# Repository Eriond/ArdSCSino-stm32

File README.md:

# Please read the following carefully:
This is a fork from the original ztto/ArdSCSino-stm32 project.\
This forks' only content are updated and modified versions of the PCB related files for the V2 version.\
The complete ztto/ArdSCSino-stm32 project is released under the MIT license, please respect that! It is only the files contained within this specific fork (Eriond/ArdSCSino-stm32) that are licensed under CC0 / Public Domain.

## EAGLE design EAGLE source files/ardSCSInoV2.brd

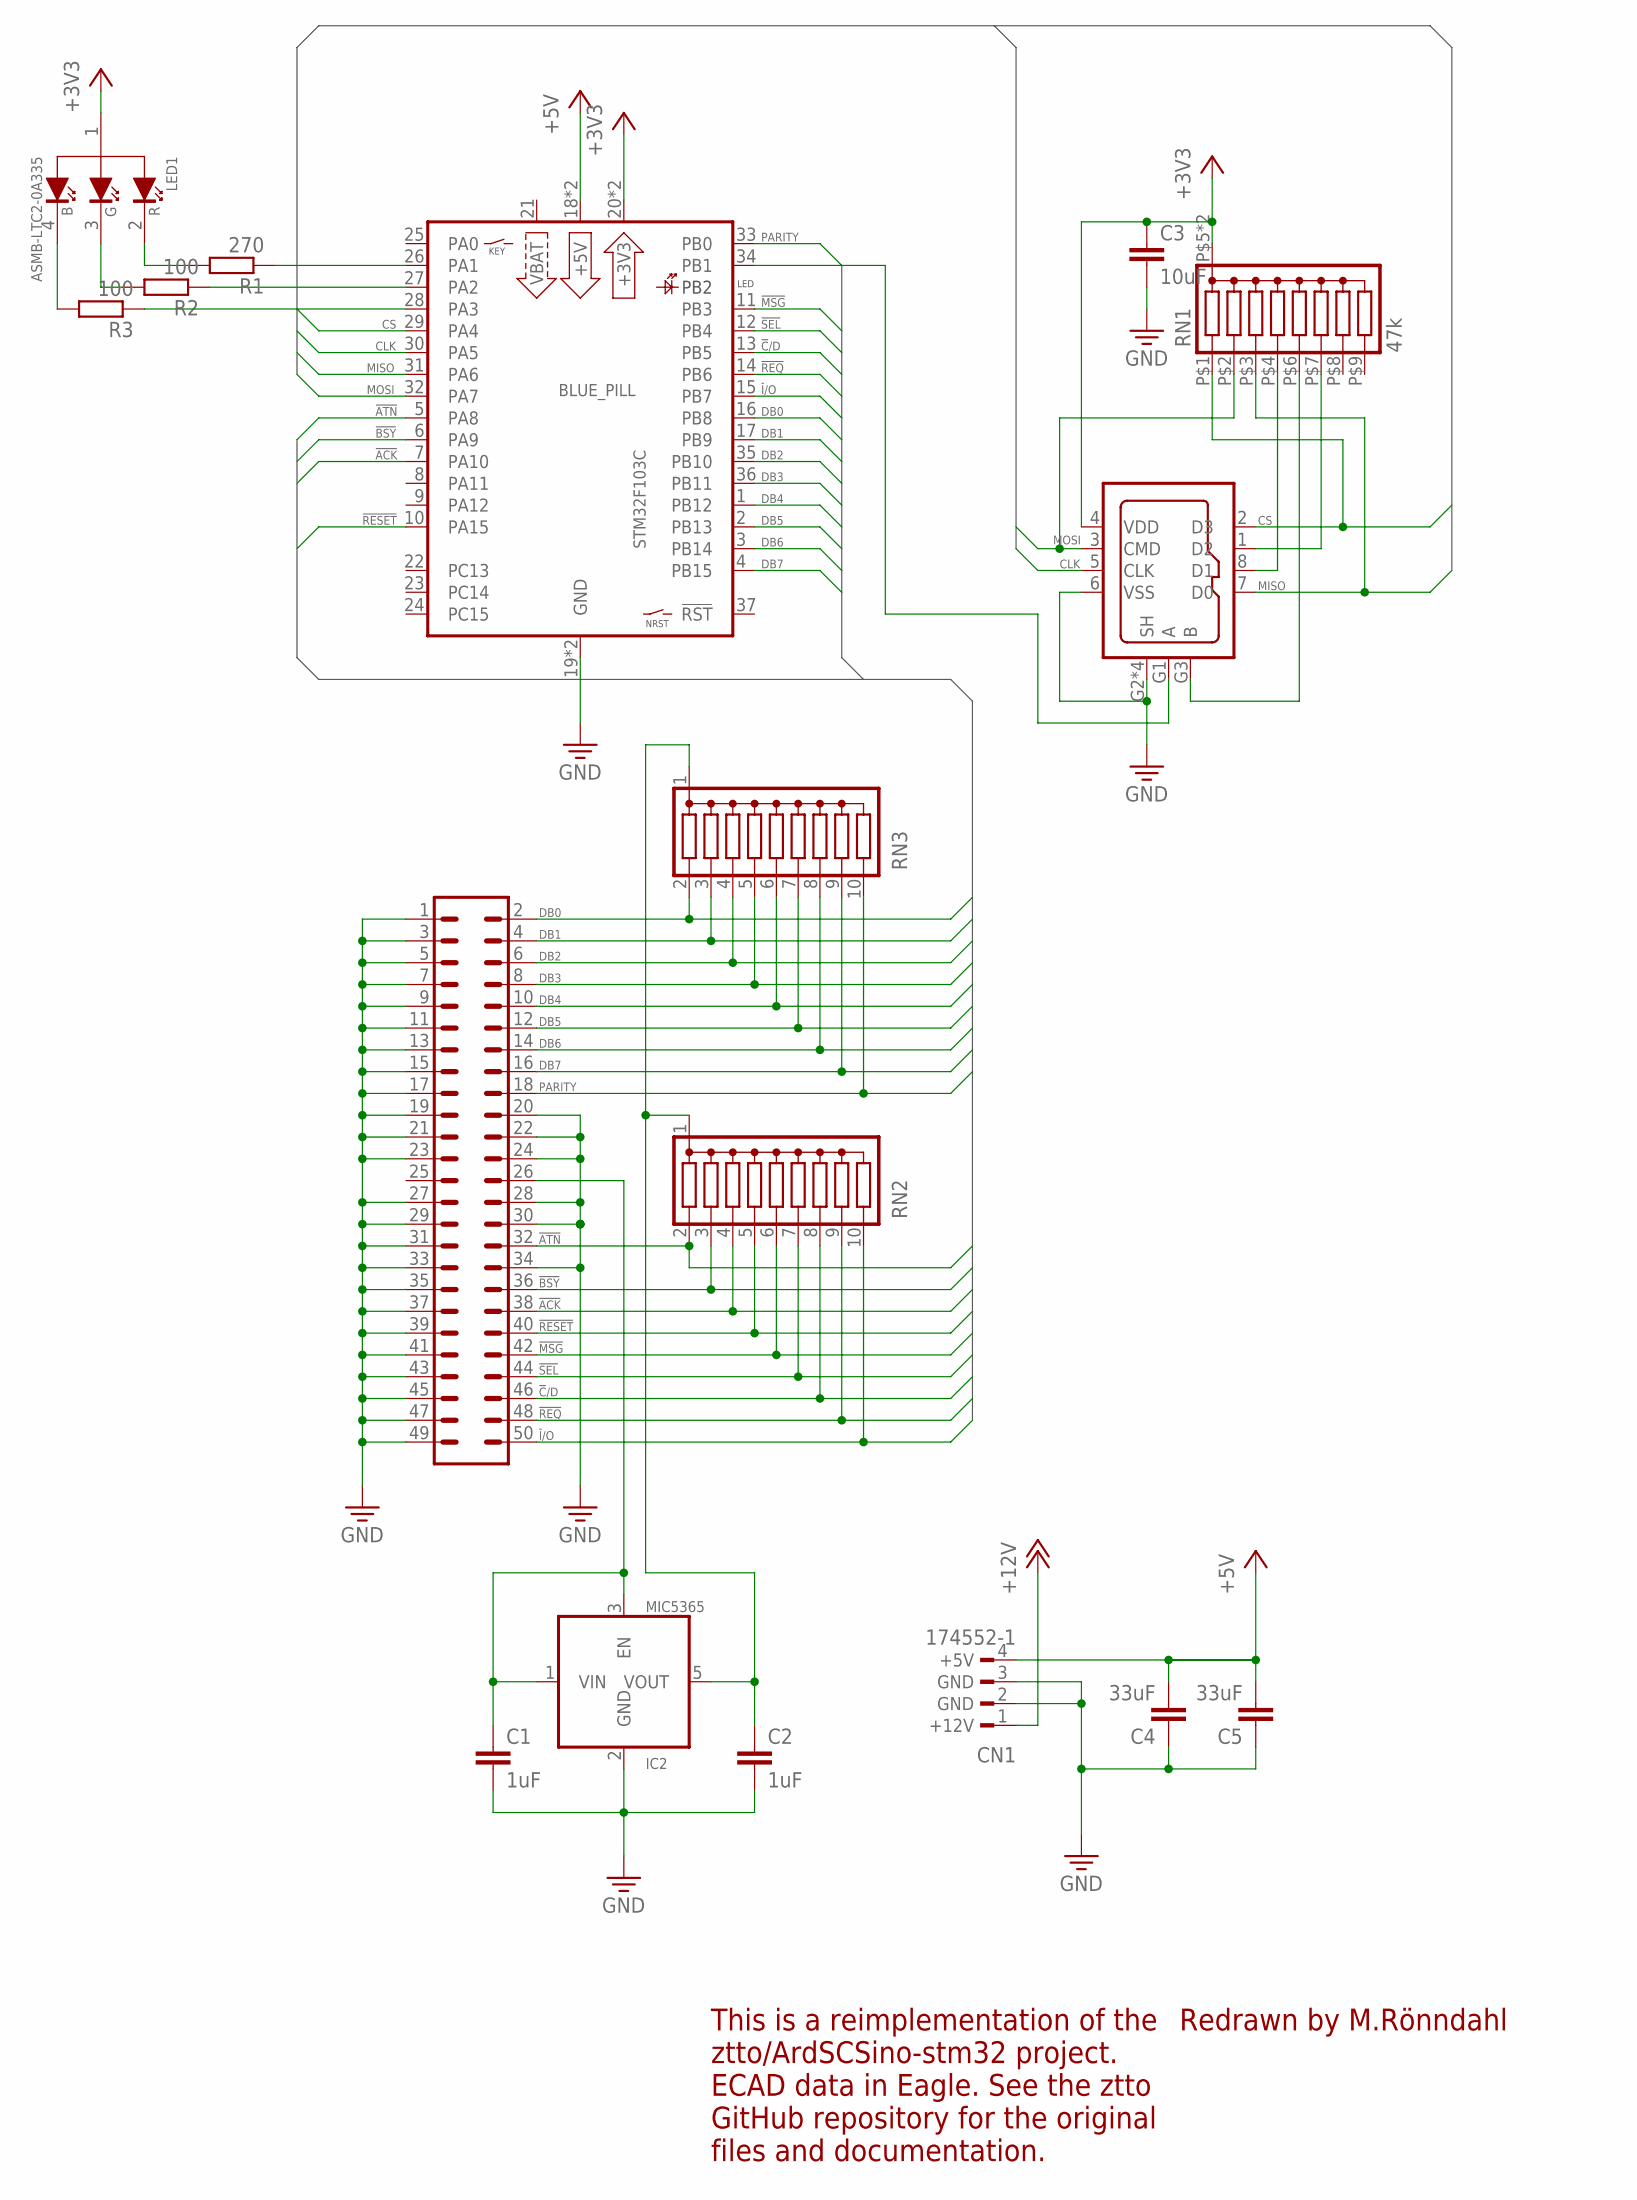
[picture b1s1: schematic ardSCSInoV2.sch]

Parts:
BLUE_PILL: STM32F103C; B-PILL
C1, C2: 1uF; C0805
C3: 10uF; C0805
C4, C5: 33uF; C0805
CN1: 174552-1
CN2: 30350-5002HB; 30350-5002
CN3: DM3AT-SF-PEJM5-PD; DM3AT-CL609
IC2: MIC5365; SOT23-5
LED1: ASMB-LTC2-0A335; PLCC-4_BROADCOM
R1: 270; R0603
R2, R3: 100; R0603
RN1: 47k; PANAS-2512
RN2, RN3: RNY9; RN-10

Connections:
!ACK: BLUE_PILL.7 (PA10), CN2.38, RN2.4 (3)
!ATN: BLUE_PILL.5 (PA8), CN2.32, RN2.2 (1)
!BSY: BLUE_PILL.6 (PA9), CN2.36, RN2.3 (2)
!C!/D: BLUE_PILL.13 (PB5), CN2.46, RN2.8 (7)
!I!/O: BLUE_PILL.15 (PB7), CN2.50, RN2.10 (9)
!MSG: BLUE_PILL.11 (PB3), CN2.42, RN2.6 (5)
!REQ: BLUE_PILL.14 (PB6), CN2.48, RN2.9 (8)
!RESET: BLUE_PILL.10 (PA15), CN2.40, RN2.5 (4)
!SEL: BLUE_PILL.12 (PB4), CN2.44, RN2.7 (6)
+3V3: BLUE_PILL.20 (+3V3), BLUE_PILL.38 (+3V3), C3.1, CN3.4 (VDD), LED1.1 (CA), RN1.P$5 (C), RN1.P$10 (C)
+5V: BLUE_PILL.18 (+5V), BLUE_PILL.40 (+5V), C4.2, C5.2, CN1.4 (+5V)
+12V: CN1.1 (+12V)
B: BLUE_PILL.28 (PA3), R3.1
CLK: BLUE_PILL.30 (PA5), CN3.5 (CLK)
CS: BLUE_PILL.29 (PA4), CN3.2 (D3), RN1.P$1 (1)
DB0: BLUE_PILL.16 (PB8), CN2.2, RN3.2 (1)
DB1: BLUE_PILL.17 (PB9), CN2.4, RN3.3 (2)
DB2: BLUE_PILL.35 (PB10), CN2.6, RN3.4 (3)
DB3: BLUE_PILL.36 (PB11), CN2.8, RN3.5 (4)
DB4: BLUE_PILL.1 (PB12), CN2.10, RN3.6 (5)
DB5: BLUE_PILL.2 (PB13), CN2.12, RN3.7 (6)
DB6: BLUE_PILL.3 (PB14), CN2.14, RN3.8 (7)
DB7: BLUE_PILL.4 (PB15), CN2.16, RN3.9 (8)
G: BLUE_PILL.27 (PA2), R2.1
GND: BLUE_PILL.19 (GND), BLUE_PILL.39 (GND), C1.2, C2.2, C3.2, C4.1, C5.1, CN1.2 (GND), CN1.3 (GND), CN2.1, CN2.3, CN2.5, CN2.7, CN2.9, CN2.11, CN2.13, CN2.15, CN2.17, CN2.19, CN2.20, CN2.21, CN2.22, CN2.23, CN2.24, CN2.27, CN2.28, CN2.29, CN2.30, CN2.31, CN2.33, CN2.34, CN2.35, CN2.37, CN2.39, CN2.41, CN2.43, CN2.45, CN2.47, CN2.49, CN3.6 (VSS), CN3.G2 (SH), CN3.G4 (SH), CN3.G5 (SH), CN3.G6 (SH), IC2.2 (GND)
MISO: BLUE_PILL.31 (PA6), CN3.7 (D0), RN1.P$3 (3)
MOSI: BLUE_PILL.32 (PA7), CN3.3 (CMD), RN1.P$2 (2)
unnamed: CN3.8 (D1), RN1.P$4 (4)
unnamed: CN3.1 (D2), RN1.P$7 (6)
unnamed: CN3.G3 (B), RN1.P$6 (5)
unnamed: BLUE_PILL.34 (PB1), CN3.G1 (A)
unnamed: LED1.4 (B), R3.2
unnamed: LED1.3 (G), R2.2
unnamed: LED1.2 (R), R1.2
PARITY: BLUE_PILL.33 (PB0), CN2.18, RN3.10 (9)
R: BLUE_PILL.26 (PA1), R1.1
TRMPWR: C1.1, CN2.26, IC2.1 (VIN), IC2.3 (EN)
VBAT: BLUE_PILL.21 (VBAT)
VOUT: C2.1, IC2.5 (VOUT), RN2.1 (C), RN3.1 (C)

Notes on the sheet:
Redrawn by M.Rönndahl
This is a reimplementation of the ztto/ArdSCSino-stm32 project. ECAD data in Eagle. See the ztto GitHub repository for the original files and documentation.

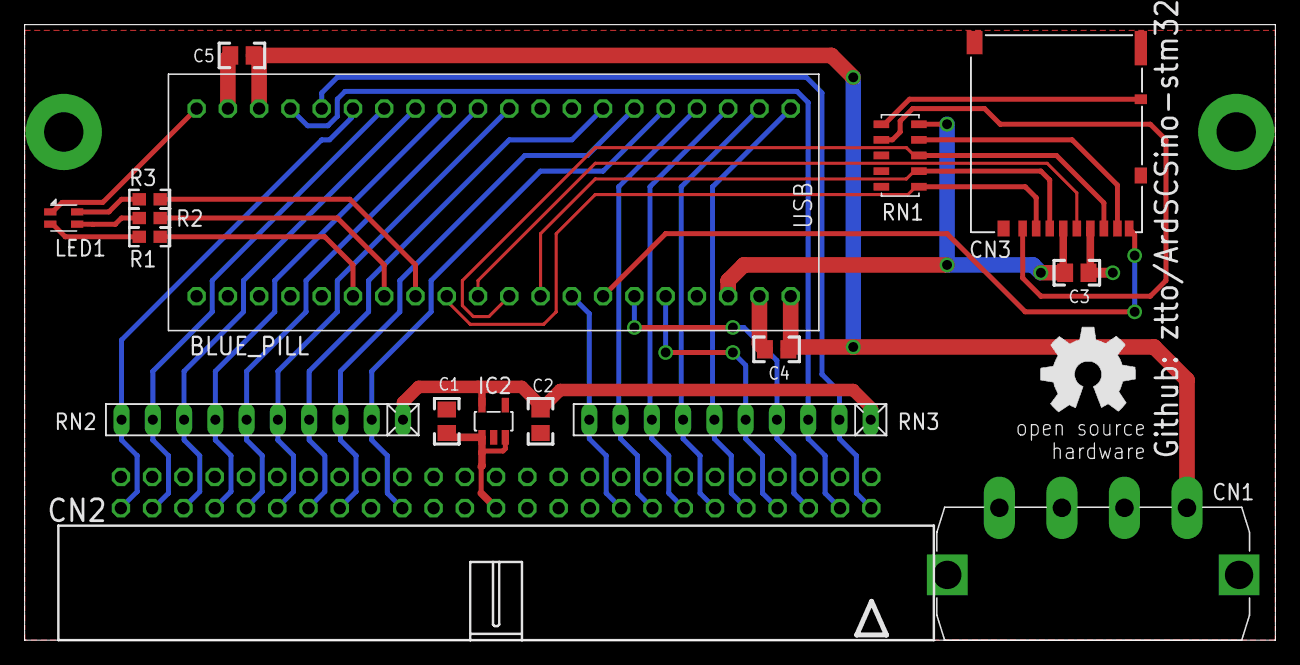
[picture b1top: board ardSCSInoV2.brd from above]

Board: 2 copper layers, 101.6 x 50.0 mm, 18 parts (0 on the bottom side), 37 nets.

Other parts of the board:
U$2: OSHW_8MM

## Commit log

2021-01-07 Update README.md
    Explained reason and goal for this fork.
2021-01-07 Delete LICENSE
    Change to CC0 license model
2021-01-07 Project file structure updated
2021-01-07 Create LICENSE
    Updated the licensing info
2021-01-10 V2 initial
    Initial commit of the V2 circuit for the BluePill board. Enhanced with active SCSI termination and a status RGB LED (optional).
